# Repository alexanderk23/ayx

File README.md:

AYX-32 28 Pin version
=====================

[Details](http://forum.tslabs.info/viewtopic.php?f=6&t=687)

[Schematics](/docs/schematics.pdf)

[Zipped Gerber files](/gerbers/gerbers.zip)

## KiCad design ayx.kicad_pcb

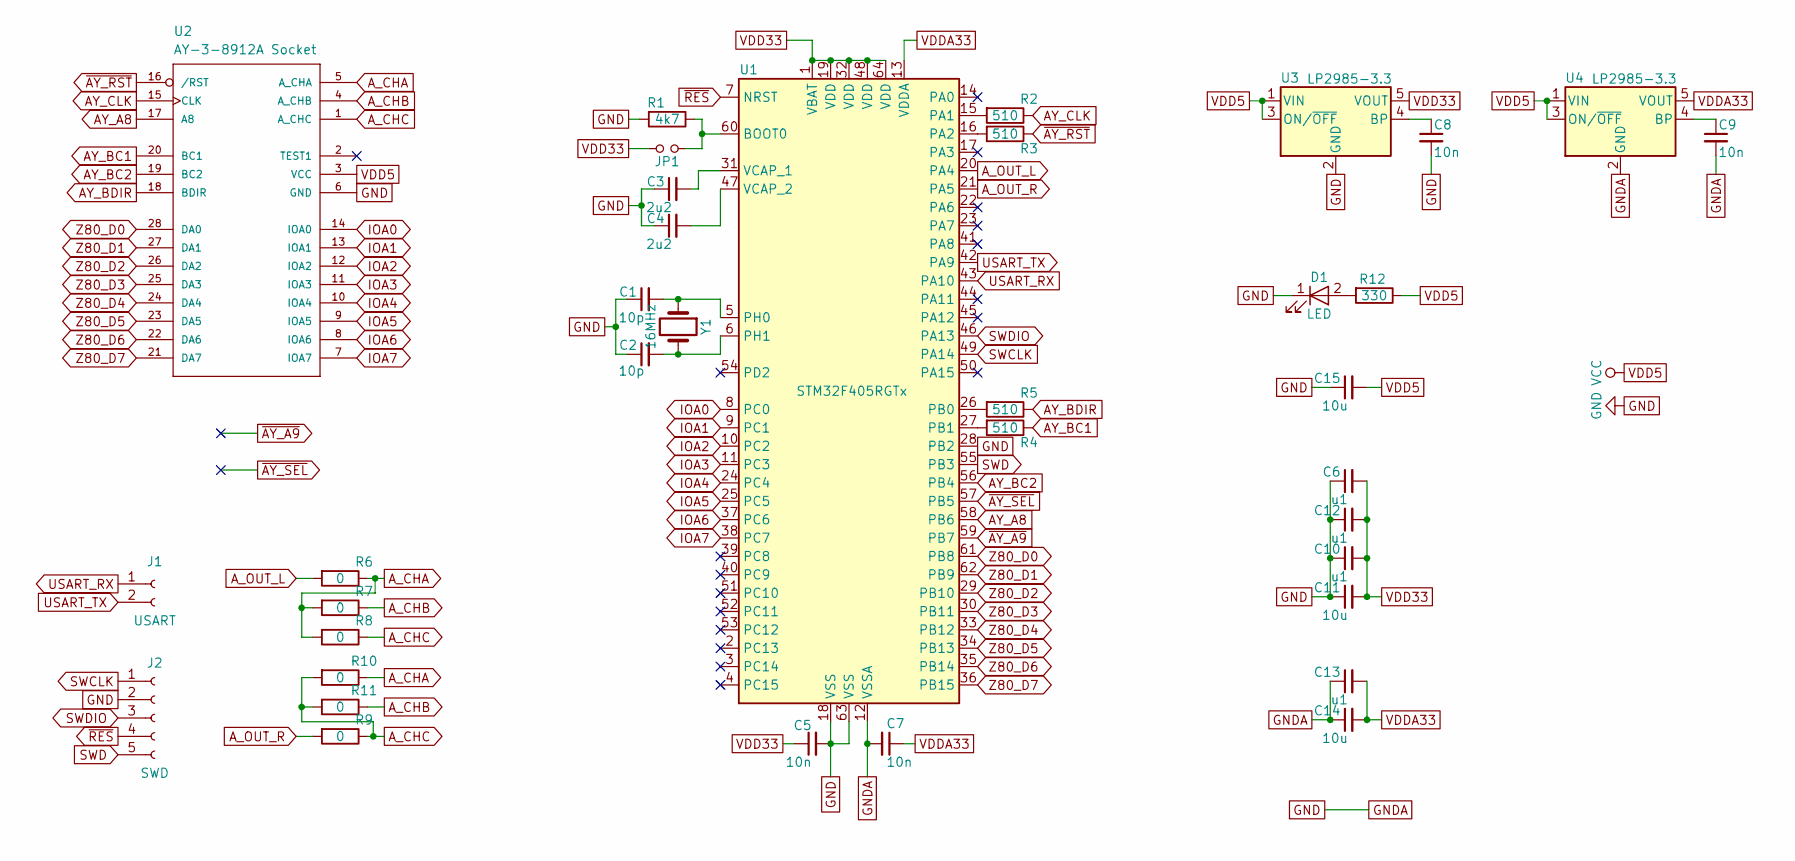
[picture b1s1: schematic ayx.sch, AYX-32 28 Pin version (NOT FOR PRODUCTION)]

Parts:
C1, C2: 10p; C_0603
C3, C4: 2u2; C_0603
C5, C7, C8, C9: 10n; C_0603
C6, C10, C12, C13: u1; C_0603
C11, C14, C15: 10u; C_0603
D1: LED; LED_0805
J1: USART
J2: SWD; Pin_Header_Straight_1x05_Pitch2.54mm
JP1: Jumper_NO_Small; Pin_Header_Straight_1x02_Pitch2.00mm
R1: 4k7; R_0603
R2, R3, R4, R5: 510; R_0603
R6, R7, R8, R9, R10, R11: 0; R_0603_HandSoldering
R12: 330; R_0603
U1: STM32F405RGTx; LQFP-64_10x10mm_P0.5mm
U2: AY-3-8912A Socket; DIL28
U3, U4: LP2985-3.3; SOT-23-5
Y1: 16MHz; Crystal_DS10_d1.0mm_l4.3mm_Horizontal

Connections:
AY_A8: U1.58 (PB6), U2.17 (A8)
AY_BC1: R4.1, U2.20 (BC1)
AY_BC2: U1.56 (PB4), U2.19 (BC2)
AY_BDIR: R5.1, U2.18 (BDIR)
AY_CLK: R2.1, U2.15 (CLK)
A_CHA: R6.1, R7.2, R8.2, R10.1, U2.5 (A_CHA)
A_CHB: R7.1, R11.1, U2.4 (A_CHB)
A_CHC: R8.1, R9.1, R10.2, R11.2, U2.1 (A_CHC)
A_OUT_L: R6.2, U1.20 (PA4)
A_OUT_R: R9.2, U1.21 (PA5)
GND: C1.1, C2.1, C3.1, C4.1, C5.2, C6.1, C7.2, C8.2, C9.2, C10.1, C11.1, C12.1, C13.1, C14.1, C15.1, D1.1 (K), J2.2, R1.2, U1.12 (VSSA), U1.18 (VSS), U1.28 (PB2), U1.63 (VSS), U2.6 (GND), U3.2 (GND), U4.2 (GND)
IOA0: U1.8 (PC0), U2.14 (IOA0)
IOA1: U1.9 (PC1), U2.13 (IOA1)
IOA2: U1.10 (PC2), U2.12 (IOA2)
IOA3: U1.11 (PC3), U2.11 (IOA3)
IOA4: U1.24 (PC4), U2.10 (IOA4)
IOA5: U1.25 (PC5), U2.9 (IOA5)
IOA6: U1.37 (PC6), U2.8 (IOA6)
IOA7: U1.38 (PC7), U2.7 (IOA7)
unnamed: C1.2, U1.5 (PH0), Y1.1
unnamed: C2.2, U1.6 (PH1), Y1.2
unnamed: C3.2, U1.31 (VCAP_1)
unnamed: C4.2, U1.47 (VCAP_2)
unnamed: C8.1, U3.4 (BP)
unnamed: C9.1, U4.4 (BP)
unnamed: D1.2 (A), R12.2
unnamed: JP1.2, R1.1, U1.60 (BOOT0)
unnamed: R2.2, U1.15 (PA1)
unnamed: R3.2, U1.16 (PA2)
unnamed: R4.2, U1.27 (PB1)
unnamed: R5.2, U1.26 (PB0)
SWCLK: J2.1, U1.49 (PA14)
SWD: J2.5, U1.55 (PB3)
SWDIO: J2.3, U1.46 (PA13)
USART_RX: J1.1, U1.43 (PA10)
USART_TX: J1.2, U1.42 (PA9)
VDD5: C15.2, R12.1, U2.3 (VCC), U3.1 (VIN), U3.3 (ON/~OFF~), U4.1 (VIN), U4.3 (ON/~OFF~)
VDD33: C5.1, C6.2, C10.2, C11.2, C12.2, JP1.1, U1.1 (VBAT), U1.19 (VDD), U1.32 (VDD), U1.48 (VDD), U1.64 (VDD), U3.5 (VOUT)
VDDA33: C7.1, C13.2, C14.2, U1.13 (VDDA), U4.5 (VOUT)
Z80_D0: U1.61 (PB8), U2.28 (DA0)
Z80_D1: U1.62 (PB9), U2.27 (DA1)
Z80_D2: U1.29 (PB10), U2.26 (DA2)
Z80_D3: U1.30 (PB11), U2.25 (DA3)
Z80_D4: U1.33 (PB12), U2.24 (DA4)
Z80_D5: U1.34 (PB13), U2.23 (DA5)
Z80_D6: U1.35 (PB14), U2.22 (DA6)
Z80_D7: U1.36 (PB15), U2.21 (DA7)
~AY_A9: U1.59 (PB7)
~AY_RST: R3.1, U2.16 (/RST)
~AY_SEL: U1.57 (PB5)
~RES: J2.4, U1.7 (NRST)

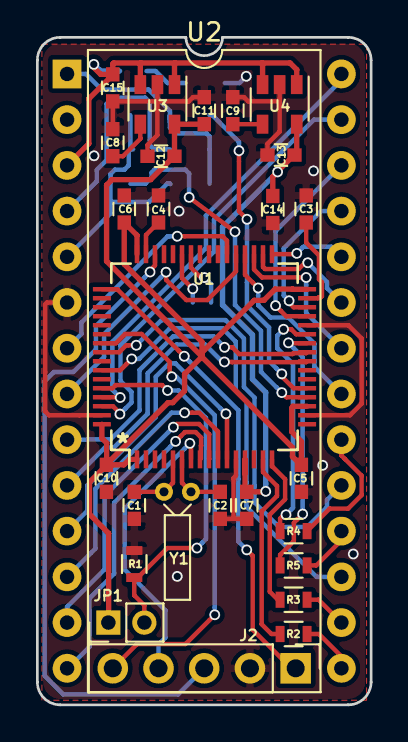
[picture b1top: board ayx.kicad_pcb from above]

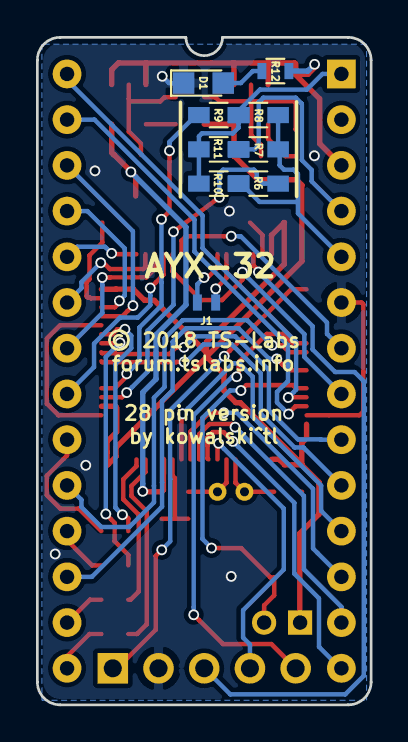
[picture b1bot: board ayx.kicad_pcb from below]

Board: 2 copper layers, 18.5 x 37.1 mm, 36 parts (9 on the bottom side), 49 nets.

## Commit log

2019-06-12 Fix some errors
2019-06-12 Update docs

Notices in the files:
ayx.kicad_pcb:
© 2018 TS-Labs
